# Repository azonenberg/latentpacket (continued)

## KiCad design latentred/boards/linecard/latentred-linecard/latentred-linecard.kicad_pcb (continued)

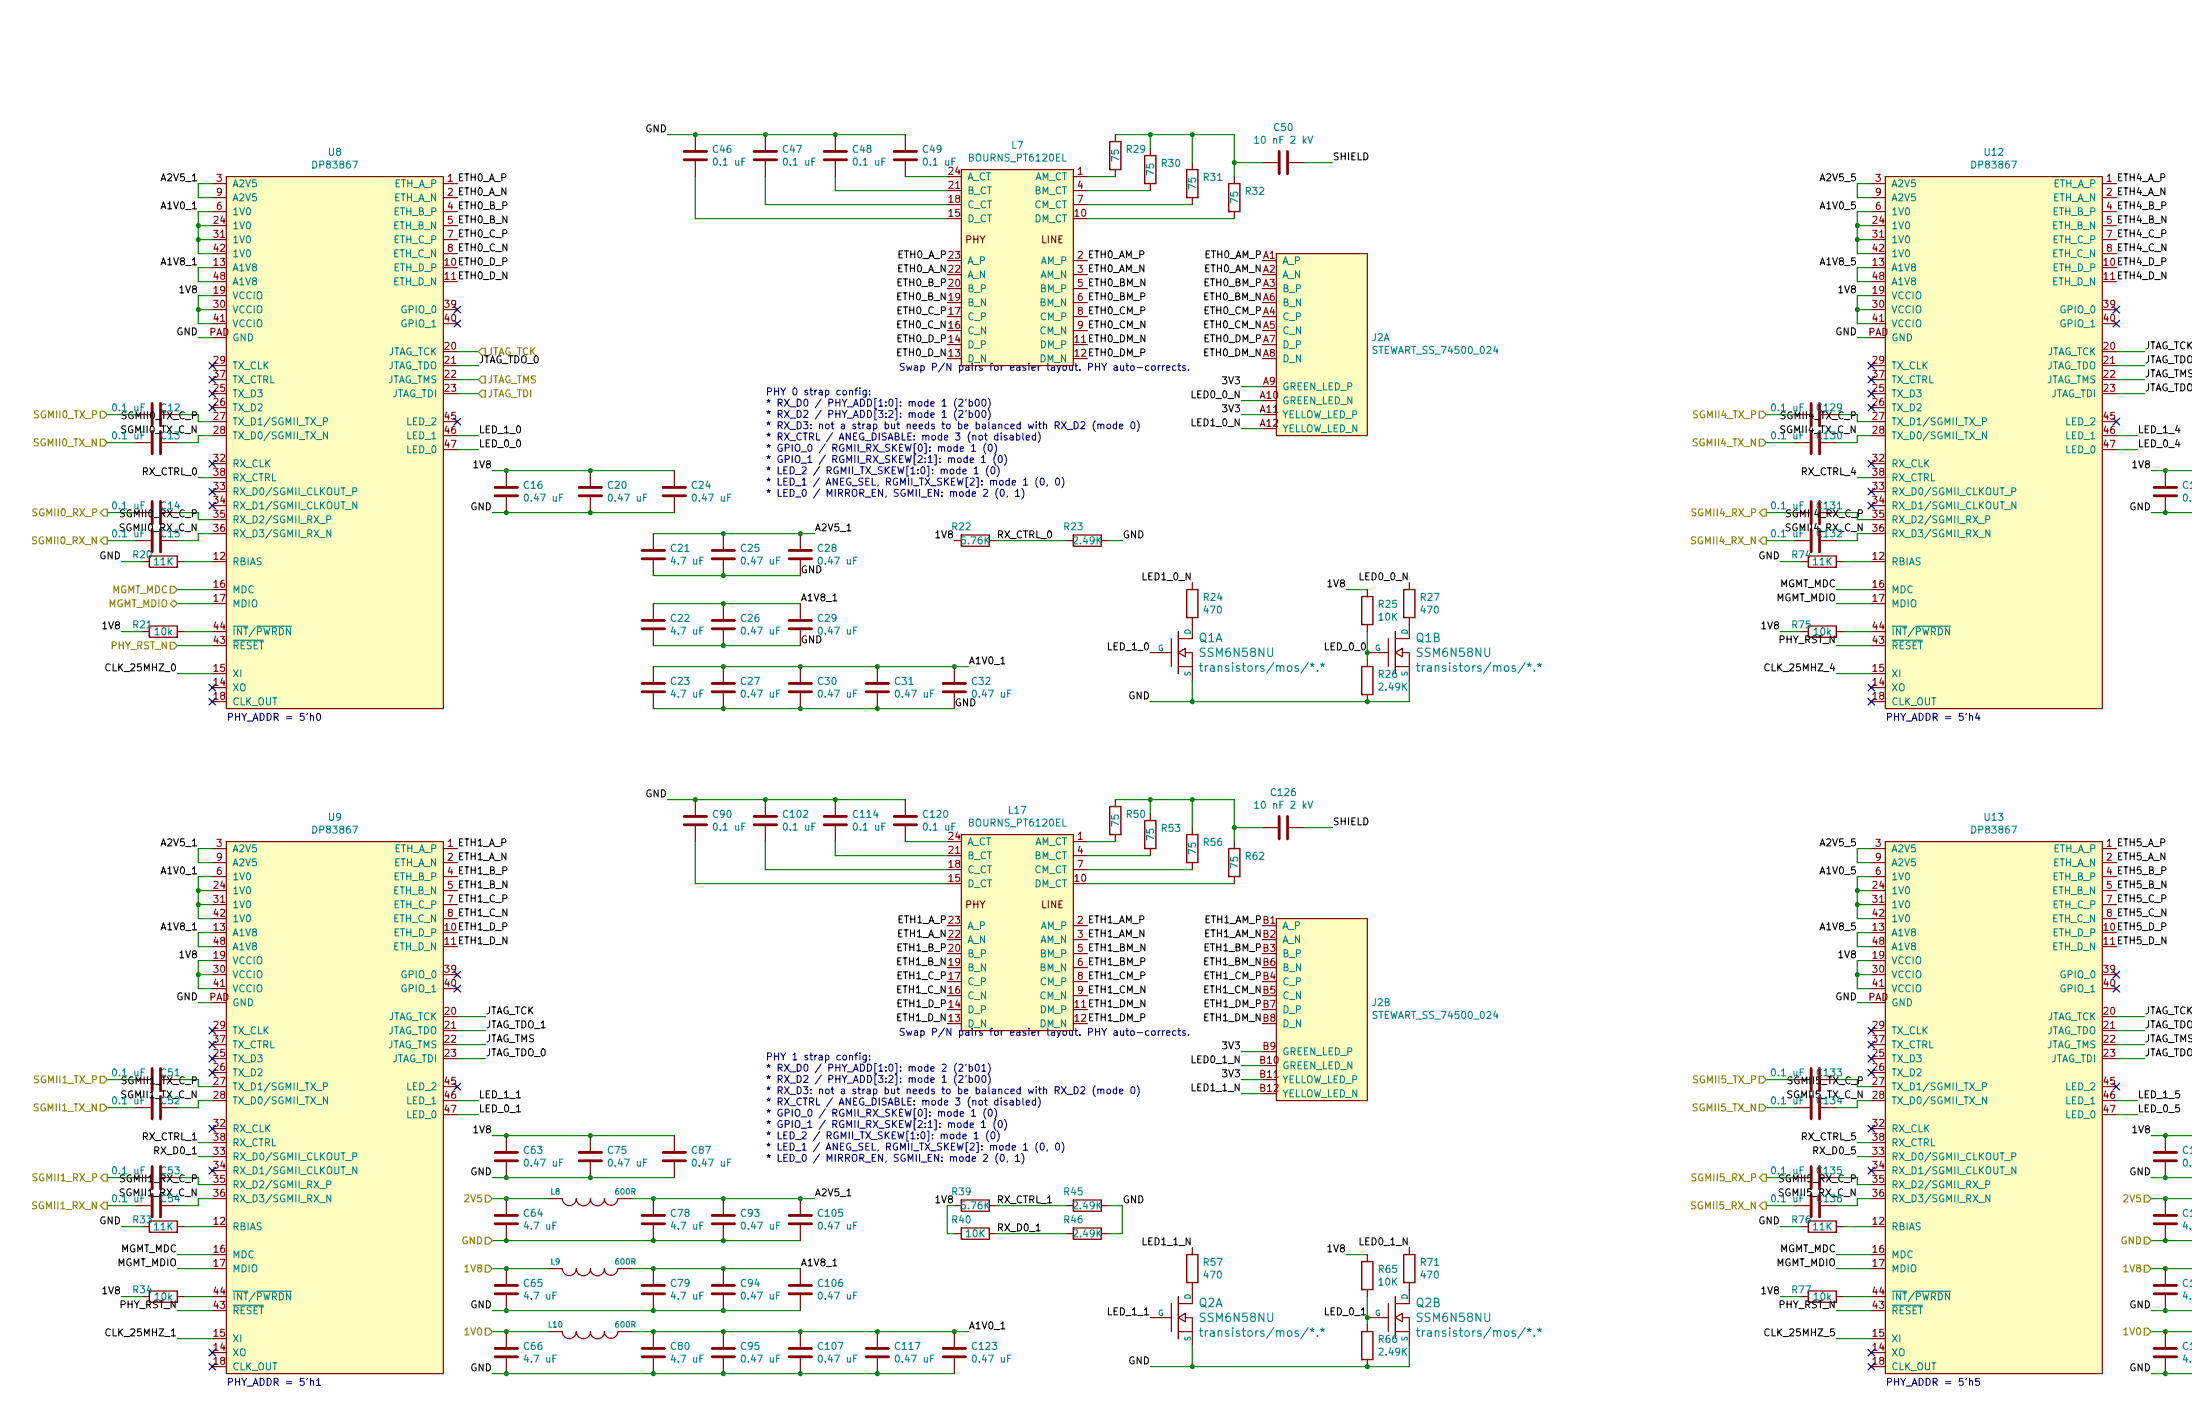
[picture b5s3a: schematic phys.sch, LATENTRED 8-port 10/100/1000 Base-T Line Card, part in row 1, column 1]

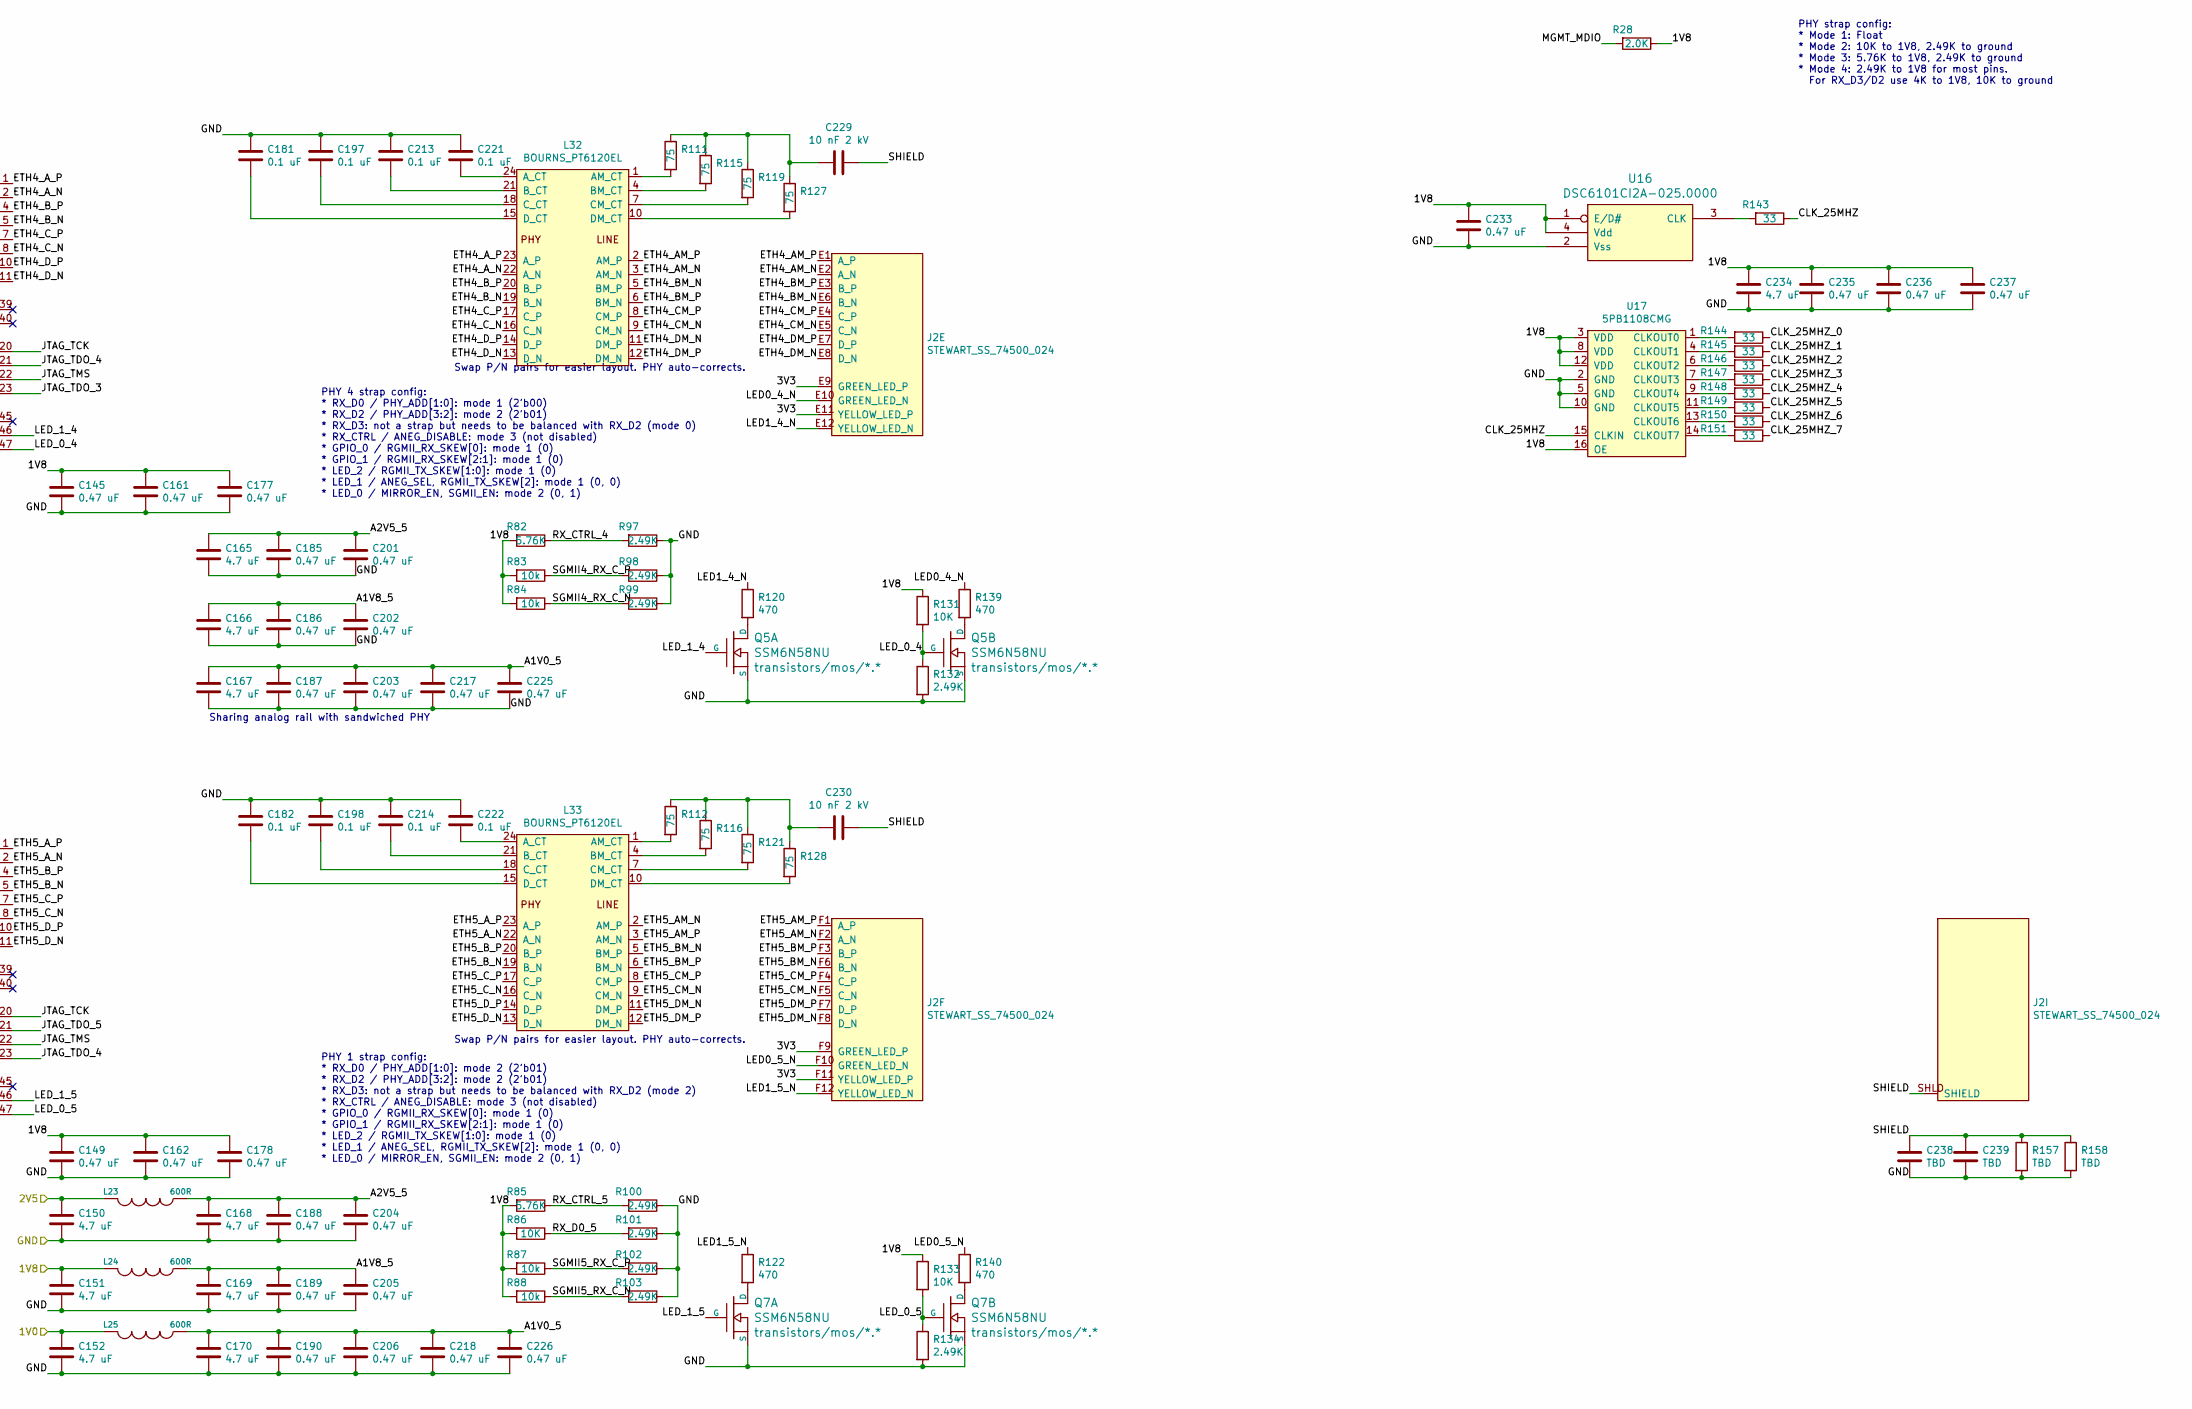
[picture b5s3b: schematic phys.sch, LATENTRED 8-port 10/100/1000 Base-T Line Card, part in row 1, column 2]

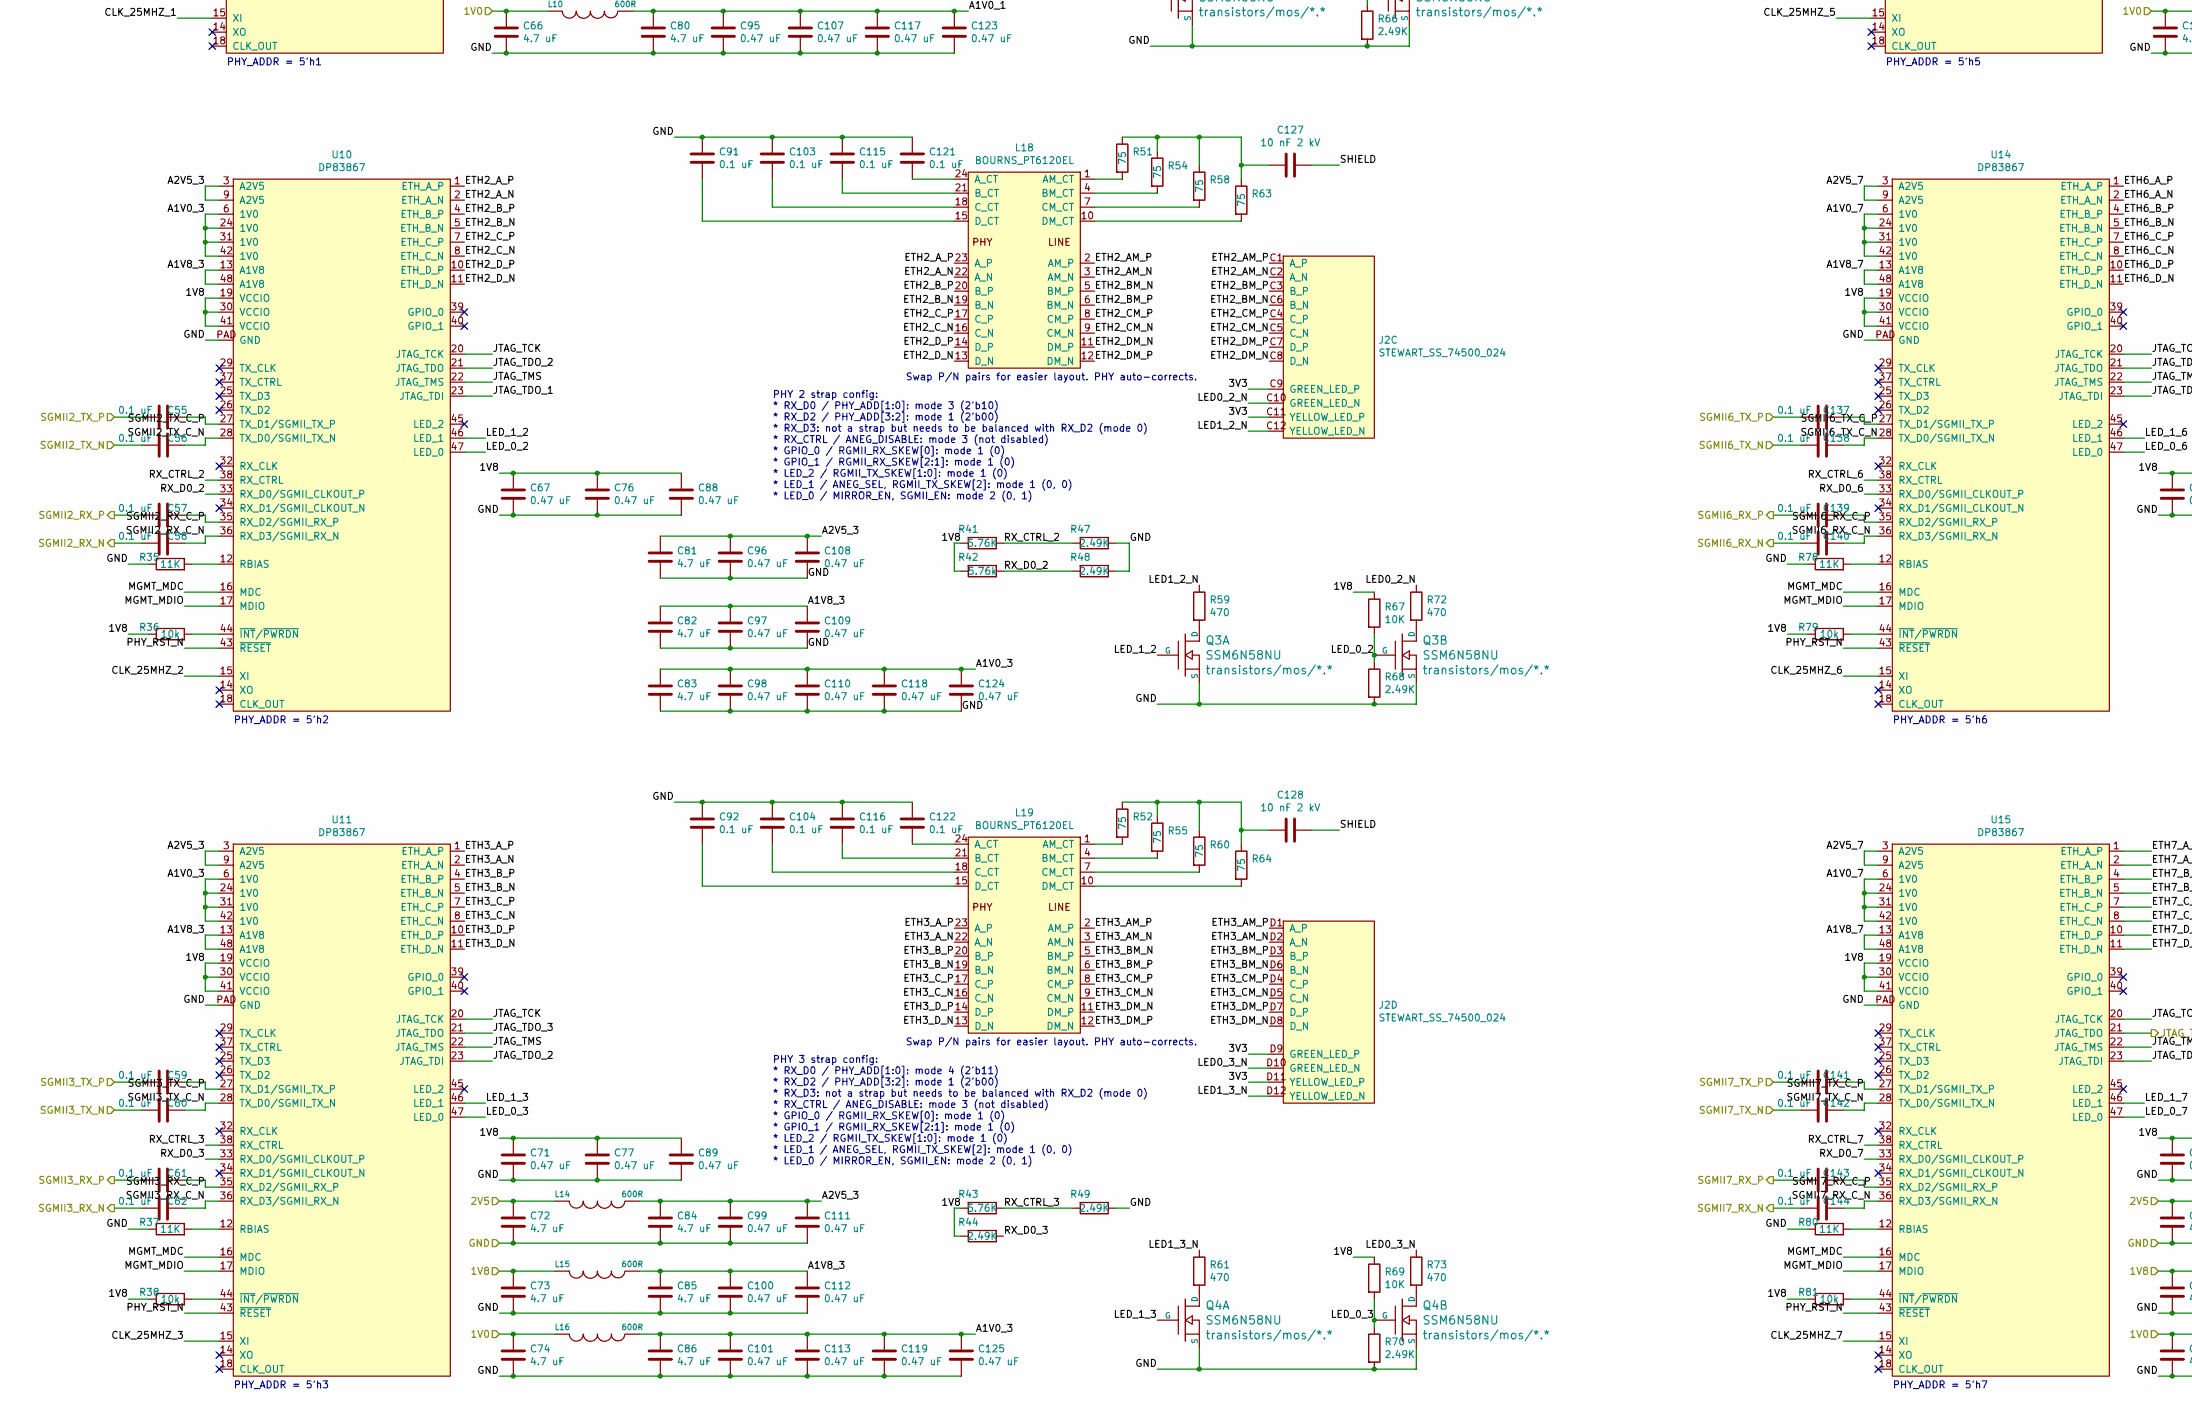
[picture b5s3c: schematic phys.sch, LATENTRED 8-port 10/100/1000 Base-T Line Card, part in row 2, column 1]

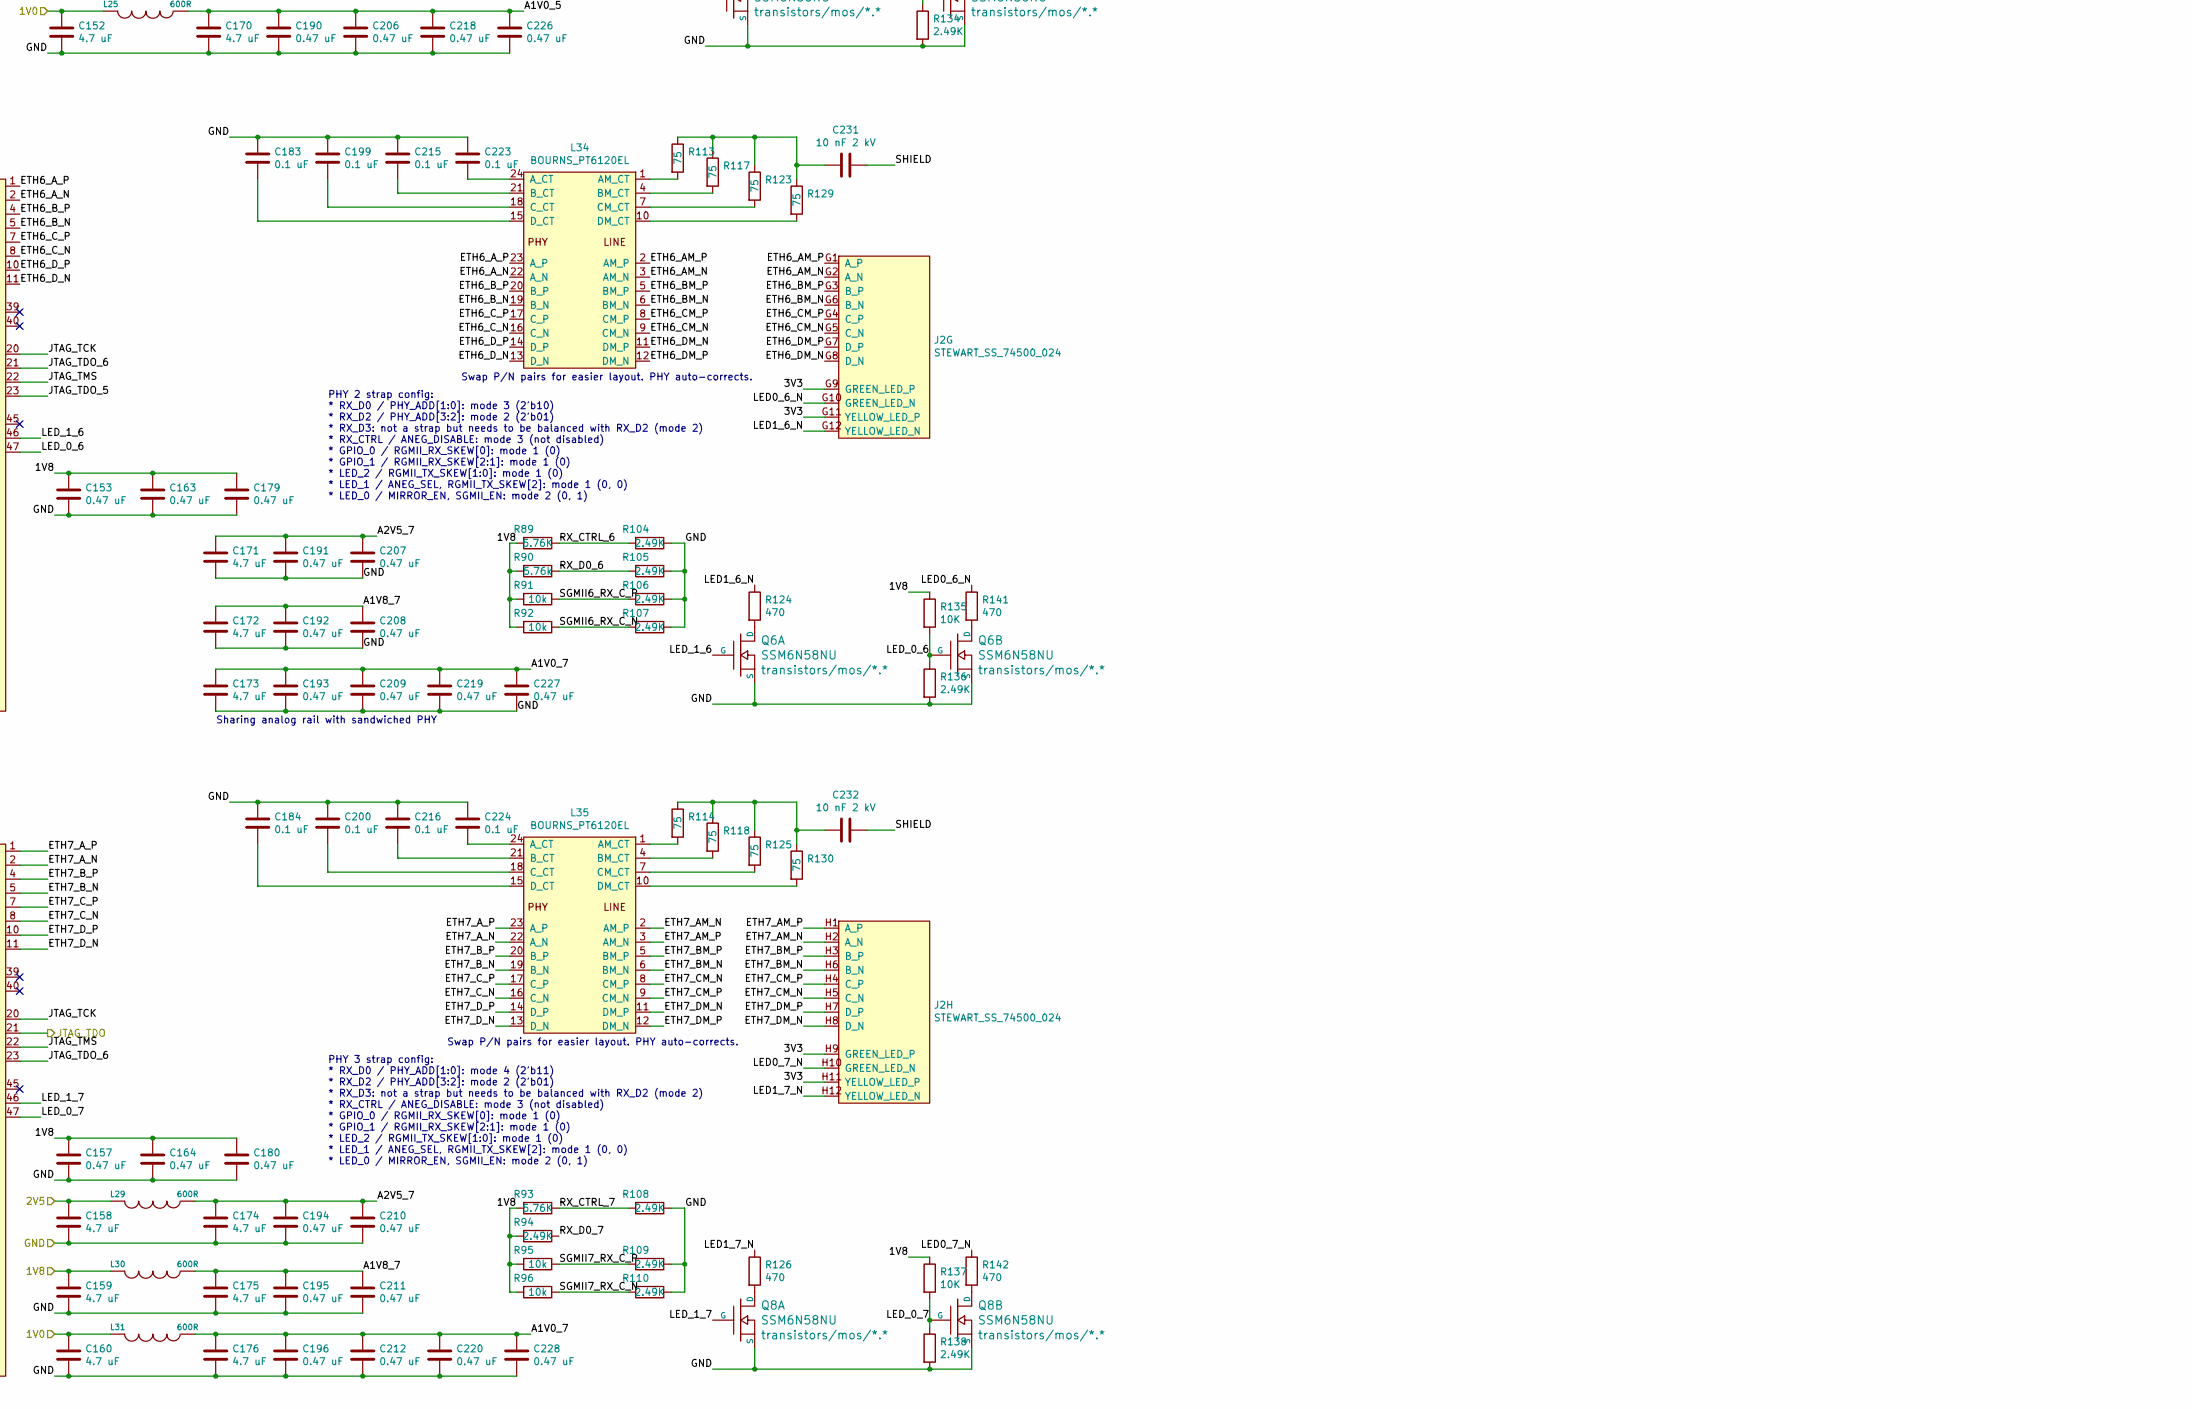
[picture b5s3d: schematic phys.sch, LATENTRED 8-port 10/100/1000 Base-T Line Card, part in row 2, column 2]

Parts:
C12, C13, C14, C15, C46, C47, C48, C49, C51, C52, C53, C54, C55, C56, C57, C58, C59, C60, C61, C62, C90, C91, C92, C102, C103, C104, C114, C115, C116, C120, C121, C122, C129, C130, C131, C132, C133, C134, C135, C136, C137, C138, C139, C140, C141, C142, C143, C144, C181, C182, C183, C184, C197, C198, C199, C200, C213, C214, C215, C216, C221, C222, C223, C224: 0.1 uF; EIA_0402_CAP_NOSILK
C16, C20, C24, C25, C26, C27, C28, C29, C30, C31, C32, C63, C67, C71, C75, C76, C77, C87, C88, C89, C93, C94, C95, C96, C97, C98, C99, C100, C101, C105, C106, C107, C108, C109, C110, C111, C112, C113, C117, C118, C119, C123, C124, C125, C145, C149, C153, C157, C161, C162, C163, C164, C177, C178, C179, C180, C185, C186, C187, C188, C189, C190, C191, C192, C193, C194, C195, C196, C201, C202, C203, C204, C205, C206, C207, C208, C209, C210, C211, C212, C217, C218, C219, C220, C225, C226, C227, C228, C233, C235, C236, C237: 0.47 uF; EIA_0402_CAP_NOSILK
C21, C22, C23, C64, C65, C66, C72, C73, C74, C78, C79, C80, C81, C82, C83, C84, C85, C86, C150, C151, C152, C158, C159, C160, C165, C166, C167, C168, C169, C170, C171, C172, C173, C174, C175, C176, C234: 4.7 uF; EIA_0603_CAP_NOSILK
C50, C126, C127, C128, C229, C230, C231, C232: 10 nF 2 kV; EIA_1812_CAP_NOSILK
C238, C239: TBD; EIA_1206_CAP_NOSILK
J2: STEWART_SS_74500_024; CONN_STEWART_SS_74500_024
L7, L17, L18, L19, L32, L33, L34, L35: BOURNS_PT6120EL; BOURNS_PT61020EL
L8, L9, L10, L14, L15, L16, L23, L24, L25, L29, L30, L31: 600R; EIA_0402_RES_NOSILK
Q1, Q2, Q3, Q4, Q5, Q6, Q7, Q8: SSM6N58NU; DFN_6_0.65MM_2x2MM_GDS
R20, R33, R35, R37, R74, R76, R78, R80: 11K; EIA_0402_RES_NOSILK
R21, R34, R36, R38, R75, R77, R79, R81, R83, R84, R87, R88, R91, R92, R95, R96: 10k; EIA_0402_RES_NOSILK
R22, R39, R41, R43, R82, R85, R89, R93: 5.76K; EIA_0402_RES_NOSILK
R23, R26, R44, R45, R46, R47, R48, R49, R66, R68, R70, R94, R97, R98, R99, R100, R101, R102, R103, R104, R105, R106, R107, R108, R109, R110, R132, R134, R136, R138: 2.49K; EIA_0402_RES_NOSILK
R24, R27, R57, R59, R61, R71, R72, R73, R120, R122, R124, R126, R139, R140, R141, R142: 470; EIA_0402_RES_NOSILK
R25, R40, R65, R67, R69, R86, R131, R133, R135, R137: 10K; EIA_0402_RES_NOSILK
R28: 2.0K; EIA_0402_RES_NOSILK
R29, R30, R31, R32, R50, R51, R52, R53, R54, R55, R56, R58, R60, R62, R63, R64, R111, R112, R113, R114, R115, R116, R117, R118, R119, R121, R123, R125, R127, R128, R129, R130: 75; EIA_0402_RES_NOSILK
R42, R90: 5.76k; EIA_0402_RES_NOSILK
R143, R144, R145, R146, R147, R148, R149, R150, R151: 33; EIA_0402_RES_NOSILK
R157, R158: TBD; EIA_1206_CAP_NOSILK
U8, U9, U10, U11, U12, U13, U14, U15: DP83867; QFN_48_0.5MM_7x7MM
U16: DSC6101CI2A-025.0000; OSCILLATOR_3.2x2.5
U17: 5PB1108CMG; QFN_16_0.4MM_2p5x2.5MM_NOPAD

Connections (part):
/GND: C16.2, C20.2, C21.2, C22.2, C23.2, C24.2, C25.2, C26.2, C27.2, C28.2, C29.2, C30.2, C31.2, C32.2, C46.1, C47.1, C48.1, C49.1, C63.2, C64.2, C65.2, C66.2, C67.2, C71.2, C72.2, C73.2, C74.2, C75.2, C76.2, C77.2, C78.2, C79.2, C80.2, C81.2, C82.2, C83.2, C84.2, C85.2, C86.2, C87.2, C88.2, C89.2, C90.1, C91.1, C92.1, C93.2, C94.2, C95.2, C96.2, C97.2, C98.2, C99.2, C100.2, C101.2, C102.1, C103.1, C104.1, C105.2, C106.2, C107.2, C108.2, C109.2, C110.2, C111.2, C112.2, C113.2, C114.1, C115.1, C116.1, C117.2, C118.2, C119.2, C120.1, C121.1, C122.1, C123.2, C124.2, C125.2, C145.2, C149.2, C150.2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; also elsewhere on the board
/JTAG_TCK: U8.20 (JTAG_TCK), U9.20 (JTAG_TCK), U10.20 (JTAG_TCK), U11.20 (JTAG_TCK), U12.20 (JTAG_TCK), U13.20 (JTAG_TCK), U14.20 (JTAG_TCK), U15.20 (JTAG_TCK); also elsewhere on the board
/JTAG_TDI: U8.23 (JTAG_TDI); also elsewhere on the board
/JTAG_TDO: U15.21 (JTAG_TDO); also elsewhere on the board
/JTAG_TMS: U8.22 (JTAG_TMS), U9.22 (JTAG_TMS), U10.22 (JTAG_TMS), U11.22 (JTAG_TMS), U12.22 (JTAG_TMS), U13.22 (JTAG_TMS), U14.22 (JTAG_TMS), U15.22 (JTAG_TMS); also elsewhere on the board
/MGMT_MDC: U8.16 (MDC), U9.16 (MDC), U10.16 (MDC), U11.16 (MDC), U12.16 (MDC), U13.16 (MDC), U14.16 (MDC), U15.16 (MDC); also elsewhere on the board
/MGMT_MDIO: R28.2, U8.17 (MDIO), U9.17 (MDIO), U10.17 (MDIO), U11.17 (MDIO), U12.17 (MDIO), U13.17 (MDIO), U14.17 (MDIO), U15.17 (MDIO); also elsewhere on the board
/PHY_RST_N: U8.43 (~RESET), U9.43 (~RESET), U10.43 (~RESET), U11.43 (~RESET), U12.43 (~RESET), U13.43 (~RESET), U14.43 (~RESET), U15.43 (~RESET); also elsewhere on the board
/PHYs/1V0: C66.1, C74.1, C152.1, C160.1, L10.2, L16.2, L25.2, L31.2; also elsewhere on the board
/PHYs/1V8: C16.1, C20.1, C24.1, C63.1, C65.1, C67.1, C71.1, C73.1, C75.1, C76.1, C77.1, C87.1, C88.1, C89.1, C145.1, C149.1, C151.1, C153.1, C157.1, C159.1, C161.1, C162.1, C163.1, C164.1, C177.1, C178.1, C179.1, C180.1, C233.1, C234.1, C235.1, C236.1, C237.1, L9.2, L15.2, L24.2, L30.2, R21.1, R22.2, R25.1, R28.1, R34.1, R36.1, R38.1, R39.2, R40.2, R41.2, R42.2, R43.2, R44.2, R65.1, R67.1, R69.1, R75.1, R77.1, R79.1, R81.1, R82.2, R83.2, R84.2, R85.2, R86.2, R87.2, R88.2, R89.2, R90.2, R91.2, R92.2, R93.2, R94.2, R95.2, R96.2, R131.1, R133.1, R135.1, R137.1, U8.19 (VCCIO), U8.30 (VCCIO), U8.41 (VCCIO), U9.19 (VCCIO), U9.30 (VCCIO)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; also elsewhere on the board
/PHYs/2V5: C64.1, C72.1, C150.1, C158.1, L8.2, L14.2, L23.2, L29.2; also elsewhere on the board
/PHYs/3V3: J2.A9 (GREEN_LED_P), J2.A11 (YELLOW_LED_P), J2.B9 (GREEN_LED_P), J2.B11 (YELLOW_LED_P), J2.C9 (GREEN_LED_P), J2.C11 (YELLOW_LED_P), J2.D9 (GREEN_LED_P), J2.D11 (YELLOW_LED_P), J2.E9 (GREEN_LED_P), J2.E11 (YELLOW_LED_P), J2.F9 (GREEN_LED_P), J2.F11 (YELLOW_LED_P), J2.G9 (GREEN_LED_P), J2.G11 (YELLOW_LED_P), J2.H9 (GREEN_LED_P), J2.H11 (YELLOW_LED_P)
/PHYs/A1V0_1: C23.1, C27.1, C30.1, C31.1, C32.1, C80.1, C95.1, C107.1, C117.1, C123.1, L10.1, U8.6 (1V0), U8.24 (1V0), U8.31 (1V0), U8.42 (1V0), U9.6 (1V0), U9.24 (1V0), U9.31 (1V0), U9.42 (1V0)
/PHYs/A1V0_3: C83.1, C86.1, C98.1, C101.1, C110.1, C113.1, C118.1, C119.1, C124.1, C125.1, L16.1, U10.6 (1V0), U10.24 (1V0), U10.31 (1V0), U10.42 (1V0), U11.6 (1V0), U11.24 (1V0), U11.31 (1V0), U11.42 (1V0)
/PHYs/A1V0_5: C167.1, C170.1, C187.1, C190.1, C203.1, C206.1, C217.1, C218.1, C225.1, C226.1, L25.1, U12.6 (1V0), U12.24 (1V0), U12.31 (1V0), U12.42 (1V0), U13.6 (1V0), U13.24 (1V0), U13.31 (1V0), U13.42 (1V0)
/PHYs/A1V0_7: C173.1, C176.1, C193.1, C196.1, C209.1, C212.1, C219.1, C220.1, C227.1, C228.1, L31.1, U14.6 (1V0), U14.24 (1V0), U14.31 (1V0), U14.42 (1V0), U15.6 (1V0), U15.24 (1V0), U15.31 (1V0), U15.42 (1V0)
/PHYs/A1V8_1: C22.1, C26.1, C29.1, C79.1, C94.1, C106.1, L9.1, U8.13 (A1V8), U8.48 (A1V8), U9.13 (A1V8), U9.48 (A1V8)
/PHYs/A1V8_3: C82.1, C85.1, C97.1, C100.1, C109.1, C112.1, L15.1, U10.13 (A1V8), U10.48 (A1V8), U11.13 (A1V8), U11.48 (A1V8)
/PHYs/A1V8_5: C166.1, C169.1, C186.1, C189.1, C202.1, C205.1, L24.1, U12.13 (A1V8), U12.48 (A1V8), U13.13 (A1V8), U13.48 (A1V8)
/PHYs/A1V8_7: C172.1, C175.1, C192.1, C195.1, C208.1, C211.1, L30.1, U14.13 (A1V8), U14.48 (A1V8), U15.13 (A1V8), U15.48 (A1V8)
/PHYs/A2V5_1: C21.1, C25.1, C28.1, C78.1, C93.1, C105.1, L8.1, U8.3 (A2V5), U8.9 (A2V5), U9.3 (A2V5), U9.9 (A2V5)
/PHYs/A2V5_3: C81.1, C84.1, C96.1, C99.1, C108.1, C111.1, L14.1, U10.3 (A2V5), U10.9 (A2V5), U11.3 (A2V5), U11.9 (A2V5)
/PHYs/A2V5_5: C165.1, C168.1, C185.1, C188.1, C201.1, C204.1, L23.1, U12.3 (A2V5), U12.9 (A2V5), U13.3 (A2V5), U13.9 (A2V5)
/PHYs/A2V5_7: C171.1, C174.1, C191.1, C194.1, C207.1, C210.1, L29.1, U14.3 (A2V5), U14.9 (A2V5), U15.3 (A2V5), U15.9 (A2V5)
/PHYs/CLK_25MHZ: R143.1, U17.15 (CLKIN)
/PHYs/CLK_25MHZ_0: R144.1, U8.15 (XI)
/PHYs/CLK_25MHZ_1: R145.1, U9.15 (XI)
/PHYs/CLK_25MHZ_2: R146.1, U10.15 (XI)
/PHYs/CLK_25MHZ_3: R147.1, U11.15 (XI)
/PHYs/CLK_25MHZ_4: R148.1, U12.15 (XI)
/PHYs/CLK_25MHZ_5: R149.1, U13.15 (XI)
/PHYs/CLK_25MHZ_6: R150.1, U14.15 (XI)
/PHYs/CLK_25MHZ_7: R151.1, U15.15 (XI)
/PHYs/ETH0_AM_N: J2.A2 (A_N), L7.3 (AM_N)
/PHYs/ETH0_AM_P: J2.A1 (A_P), L7.2 (AM_P)
/PHYs/ETH0_A_N: L7.22 (A_N), U8.2 (ETH_A_N)
/PHYs/ETH0_A_P: L7.23 (A_P), U8.1 (ETH_A_P)
/PHYs/ETH0_BM_N: J2.A6 (B_N), L7.5 (BM_P)
/PHYs/ETH0_BM_P: J2.A3 (B_P), L7.6 (BM_N)
/PHYs/ETH0_B_N: L7.19 (B_N), U8.5 (ETH_B_N)
/PHYs/ETH0_B_P: L7.20 (B_P), U8.4 (ETH_B_P)
/PHYs/ETH0_CM_N: J2.A5 (C_N), L7.9 (CM_N)
/PHYs/ETH0_CM_P: J2.A4 (C_P), L7.8 (CM_P)
/PHYs/ETH0_C_N: L7.16 (C_N), U8.8 (ETH_C_N)
/PHYs/ETH0_C_P: L7.17 (C_P), U8.7 (ETH_C_P)
/PHYs/ETH0_DM_N: J2.A8 (D_N), L7.11 (DM_P)
/PHYs/ETH0_DM_P: J2.A7 (D_P), L7.12 (DM_N)
/PHYs/ETH0_D_N: L7.13 (D_N), U8.11 (ETH_D_N)
/PHYs/ETH0_D_P: L7.14 (D_P), U8.10 (ETH_D_P)
/PHYs/ETH1_AM_N: J2.B2 (A_N), L17.3 (AM_N)
/PHYs/ETH1_AM_P: J2.B1 (A_P), L17.2 (AM_P)
/PHYs/ETH1_A_N: L17.22 (A_N), U9.2 (ETH_A_N)
/PHYs/ETH1_A_P: L17.23 (A_P), U9.1 (ETH_A_P)
/PHYs/ETH1_BM_N: J2.B6 (B_N), L17.5 (BM_P)
/PHYs/ETH1_BM_P: J2.B3 (B_P), L17.6 (BM_N)
/PHYs/ETH1_B_N: L17.19 (B_N), U9.5 (ETH_B_N)
/PHYs/ETH1_B_P: L17.20 (B_P), U9.4 (ETH_B_P)
/PHYs/ETH1_CM_N: J2.B5 (C_N), L17.9 (CM_N)
/PHYs/ETH1_CM_P: J2.B4 (C_P), L17.8 (CM_P)
/PHYs/ETH1_C_N: L17.16 (C_N), U9.8 (ETH_C_N)
/PHYs/ETH1_C_P: L17.17 (C_P), U9.7 (ETH_C_P)
/PHYs/ETH1_DM_N: J2.B8 (D_N), L17.11 (DM_P)
/PHYs/ETH1_DM_P: J2.B7 (D_P), L17.12 (DM_N)
/PHYs/ETH1_D_N: L17.13 (D_N), U9.11 (ETH_D_N)
/PHYs/ETH1_D_P: L17.14 (D_P), U9.10 (ETH_D_P)
/PHYs/ETH2_AM_N: J2.C2 (A_N), L18.3 (AM_N)
/PHYs/ETH2_AM_P: J2.C1 (A_P), L18.2 (AM_P)
/PHYs/ETH2_A_N: L18.22 (A_N), U10.2 (ETH_A_N)
/PHYs/ETH2_A_P: L18.23 (A_P), U10.1 (ETH_A_P)
/PHYs/ETH2_BM_N: J2.C6 (B_N), L18.5 (BM_P)
/PHYs/ETH2_BM_P: J2.C3 (B_P), L18.6 (BM_N)
/PHYs/ETH2_B_N: L18.19 (B_N), U10.5 (ETH_B_N)
/PHYs/ETH2_B_P: L18.20 (B_P), U10.4 (ETH_B_P)
/PHYs/ETH2_CM_N: J2.C5 (C_N), L18.9 (CM_N)
/PHYs/ETH2_CM_P: J2.C4 (C_P), L18.8 (CM_P)
/PHYs/ETH2_C_N: L18.16 (C_N), U10.8 (ETH_C_N)
/PHYs/ETH2_C_P: L18.17 (C_P), U10.7 (ETH_C_P)
/PHYs/ETH2_DM_N: J2.C8 (D_N), L18.11 (DM_P)
/PHYs/ETH2_DM_P: J2.C7 (D_P), L18.12 (DM_N)
/PHYs/ETH2_D_N: L18.13 (D_N), U10.11 (ETH_D_N)
/PHYs/ETH2_D_P: L18.14 (D_P), U10.10 (ETH_D_P)
/PHYs/ETH3_AM_N: J2.D2 (A_N), L19.3 (AM_N)
/PHYs/ETH3_AM_P: J2.D1 (A_P), L19.2 (AM_P)
/PHYs/ETH3_A_N: L19.22 (A_N), U11.2 (ETH_A_N)
/PHYs/ETH3_A_P: L19.23 (A_P), U11.1 (ETH_A_P)
/PHYs/ETH3_BM_N: J2.D6 (B_N), L19.5 (BM_P)
/PHYs/ETH3_BM_P: J2.D3 (B_P), L19.6 (BM_N)
/PHYs/ETH3_B_N: L19.19 (B_N), U11.5 (ETH_B_N)
/PHYs/ETH3_B_P: L19.20 (B_P), U11.4 (ETH_B_P)
/PHYs/ETH3_CM_N: J2.D5 (C_N), L19.9 (CM_N)
/PHYs/ETH3_CM_P: J2.D4 (C_P), L19.8 (CM_P)
/PHYs/ETH3_C_N: L19.16 (C_N), U11.8 (ETH_C_N)
/PHYs/ETH3_C_P: L19.17 (C_P), U11.7 (ETH_C_P)
/PHYs/ETH3_DM_N: J2.D8 (D_N), L19.11 (DM_P)
/PHYs/ETH3_DM_P: J2.D7 (D_P), L19.12 (DM_N)
/PHYs/ETH3_D_N: L19.13 (D_N), U11.11 (ETH_D_N)
/PHYs/ETH3_D_P: L19.14 (D_P), U11.10 (ETH_D_P)
/PHYs/ETH4_AM_N: J2.E2 (A_N), L32.3 (AM_N)
/PHYs/ETH4_AM_P: J2.E1 (A_P), L32.2 (AM_P)
/PHYs/ETH4_A_N: L32.22 (A_N), U12.2 (ETH_A_N)
/PHYs/ETH4_A_P: L32.23 (A_P), U12.1 (ETH_A_P)
/PHYs/ETH4_BM_N: J2.E6 (B_N), L32.5 (BM_P)
/PHYs/ETH4_BM_P: J2.E3 (B_P), L32.6 (BM_N)
/PHYs/ETH4_B_N: L32.19 (B_N), U12.5 (ETH_B_N)
/PHYs/ETH4_B_P: L32.20 (B_P), U12.4 (ETH_B_P)
/PHYs/ETH4_CM_N: J2.E5 (C_N), L32.9 (CM_N)
/PHYs/ETH4_CM_P: J2.E4 (C_P), L32.8 (CM_P)
/PHYs/ETH4_C_N: L32.16 (C_N), U12.8 (ETH_C_N)
/PHYs/ETH4_C_P: L32.17 (C_P), U12.7 (ETH_C_P)
/PHYs/ETH4_DM_N: J2.E8 (D_N), L32.11 (DM_P)
/PHYs/ETH4_DM_P: J2.E7 (D_P), L32.12 (DM_N)
/PHYs/ETH4_D_N: L32.13 (D_N), U12.11 (ETH_D_N)
/PHYs/ETH4_D_P: L32.14 (D_P), U12.10 (ETH_D_P)
/PHYs/ETH5_AM_N: J2.F2 (A_N), L33.2 (AM_P)
/PHYs/ETH5_AM_P: J2.F1 (A_P), L33.3 (AM_N)
/PHYs/ETH5_A_N: L33.22 (A_N), U13.2 (ETH_A_N)
/PHYs/ETH5_A_P: L33.23 (A_P), U13.1 (ETH_A_P)
/PHYs/ETH5_BM_N: J2.F6 (B_N), L33.5 (BM_P)
/PHYs/ETH5_BM_P: J2.F3 (B_P), L33.6 (BM_N)
/PHYs/ETH5_B_N: L33.19 (B_N), U13.5 (ETH_B_N)
/PHYs/ETH5_B_P: L33.20 (B_P), U13.4 (ETH_B_P)
/PHYs/ETH5_CM_N: J2.F5 (C_N), L33.9 (CM_N)
/PHYs/ETH5_CM_P: J2.F4 (C_P), L33.8 (CM_P)
/PHYs/ETH5_C_N: L33.16 (C_N), U13.8 (ETH_C_N)
/PHYs/ETH5_C_P: L33.17 (C_P), U13.7 (ETH_C_P)
/PHYs/ETH5_DM_N: J2.F8 (D_N), L33.11 (DM_P)
/PHYs/ETH5_DM_P: J2.F7 (D_P), L33.12 (DM_N)
/PHYs/ETH5_D_N: L33.13 (D_N), U13.11 (ETH_D_N)
/PHYs/ETH5_D_P: L33.14 (D_P), U13.10 (ETH_D_P)
/PHYs/ETH6_AM_N: J2.G2 (A_N), L34.3 (AM_N)
/PHYs/ETH6_AM_P: J2.G1 (A_P), L34.2 (AM_P)
/PHYs/ETH6_A_N: L34.22 (A_N), U14.2 (ETH_A_N)
/PHYs/ETH6_A_P: L34.23 (A_P), U14.1 (ETH_A_P)
/PHYs/ETH6_BM_N: J2.G6 (B_N), L34.6 (BM_N)
/PHYs/ETH6_BM_P: J2.G3 (B_P), L34.5 (BM_P)
/PHYs/ETH6_B_N: L34.19 (B_N), U14.5 (ETH_B_N)
/PHYs/ETH6_B_P: L34.20 (B_P), U14.4 (ETH_B_P)
/PHYs/ETH6_CM_N: J2.G5 (C_N), L34.9 (CM_N)
/PHYs/ETH6_CM_P: J2.G4 (C_P), L34.8 (CM_P)
/PHYs/ETH6_C_N: L34.16 (C_N), U14.8 (ETH_C_N)
/PHYs/ETH6_C_P: L34.17 (C_P), U14.7 (ETH_C_P)
/PHYs/ETH6_DM_N: J2.G8 (D_N), L34.11 (DM_P)
/PHYs/ETH6_DM_P: J2.G7 (D_P), L34.12 (DM_N)
/PHYs/ETH6_D_N: L34.13 (D_N), U14.11 (ETH_D_N)
/PHYs/ETH6_D_P: L34.14 (D_P), U14.10 (ETH_D_P)
/PHYs/ETH7_AM_N: J2.H2 (A_N), L35.2 (AM_P)
/PHYs/ETH7_AM_P: J2.H1 (A_P), L35.3 (AM_N)
/PHYs/ETH7_A_N: L35.22 (A_N), U15.2 (ETH_A_N)
/PHYs/ETH7_A_P: L35.23 (A_P), U15.1 (ETH_A_P)
/PHYs/ETH7_BM_N: J2.H6 (B_N), L35.6 (BM_N)
/PHYs/ETH7_BM_P: J2.H3 (B_P), L35.5 (BM_P)
/PHYs/ETH7_B_N: L35.19 (B_N), U15.5 (ETH_B_N)
/PHYs/ETH7_B_P: L35.20 (B_P), U15.4 (ETH_B_P)
/PHYs/ETH7_CM_N: J2.H5 (C_N), L35.8 (CM_P)
/PHYs/ETH7_CM_P: J2.H4 (C_P), L35.9 (CM_N)
/PHYs/ETH7_C_N: L35.16 (C_N), U15.8 (ETH_C_N)
/PHYs/ETH7_C_P: L35.17 (C_P), U15.7 (ETH_C_P)
/PHYs/ETH7_DM_N: J2.H8 (D_N), L35.11 (DM_P)
/PHYs/ETH7_DM_P: J2.H7 (D_P), L35.12 (DM_N)
/PHYs/ETH7_D_N: L35.13 (D_N), U15.11 (ETH_D_N)
/PHYs/ETH7_D_P: L35.14 (D_P), U15.10 (ETH_D_P)
/PHYs/JTAG_TDO_0: U8.21 (JTAG_TDO), U9.23 (JTAG_TDI)
/PHYs/JTAG_TDO_1: U9.21 (JTAG_TDO), U10.23 (JTAG_TDI)
/PHYs/JTAG_TDO_2: U10.21 (JTAG_TDO), U11.23 (JTAG_TDI)
/PHYs/JTAG_TDO_3: U11.21 (JTAG_TDO), U12.23 (JTAG_TDI)
/PHYs/JTAG_TDO_4: U12.21 (JTAG_TDO), U13.23 (JTAG_TDI)
/PHYs/JTAG_TDO_5: U13.21 (JTAG_TDO), U14.23 (JTAG_TDI)
/PHYs/JTAG_TDO_6: U14.21 (JTAG_TDO), U15.23 (JTAG_TDI)
/PHYs/LED0_0_N: J2.A10 (GREEN_LED_N), R27.1
/PHYs/LED0_1_N: J2.B10 (GREEN_LED_N), R71.1
/PHYs/LED0_2_N: J2.C10 (GREEN_LED_N), R72.1
/PHYs/LED0_3_N: J2.D10 (GREEN_LED_N), R73.1
/PHYs/LED0_4_N: J2.E10 (GREEN_LED_N), R139.1
/PHYs/LED0_5_N: J2.F10 (GREEN_LED_N), R140.1
/PHYs/LED0_6_N: J2.G10 (GREEN_LED_N), R141.1
/PHYs/LED0_7_N: J2.H10 (GREEN_LED_N), R142.1
/PHYs/LED1_0_N: J2.A12 (YELLOW_LED_N), R24.1
/PHYs/LED1_1_N: J2.B12 (YELLOW_LED_N), R57.1
/PHYs/LED1_2_N: J2.C12 (YELLOW_LED_N), R59.1
/PHYs/LED1_3_N: J2.D12 (YELLOW_LED_N), R61.1
/PHYs/LED1_4_N: J2.E12 (YELLOW_LED_N), R120.1
/PHYs/LED1_5_N: J2.F12 (YELLOW_LED_N), R122.1
/PHYs/LED1_6_N: J2.G12 (YELLOW_LED_N), R124.1
/PHYs/LED1_7_N: J2.H12 (YELLOW_LED_N), R126.1
/PHYs/LED_0_0: Q1.G2 (G), R25.2, R26.1, U8.47 (LED_0)
/PHYs/LED_0_1: Q2.G2 (G), R65.2, R66.1, U9.47 (LED_0)
/PHYs/LED_0_2: Q3.G2 (G), R67.2, R68.1, U10.47 (LED_0)
/PHYs/LED_0_3: Q4.G2 (G), R69.2, R70.1, U11.47 (LED_0)
/PHYs/LED_0_4: Q5.G2 (G), R131.2, R132.1, U12.47 (LED_0)
/PHYs/LED_0_5: Q7.G2 (G), R133.2, R134.1, U13.47 (LED_0)
/PHYs/LED_0_6: Q6.G2 (G), R135.2, R136.1, U14.47 (LED_0)
/PHYs/LED_0_7: Q8.G2 (G), R137.2, R138.1, U15.47 (LED_0)
/PHYs/LED_1_0: Q1.G1 (G), U8.46 (LED_1)
/PHYs/LED_1_1: Q2.G1 (G), U9.46 (LED_1)
/PHYs/LED_1_2: Q3.G1 (G), U10.46 (LED_1)
/PHYs/LED_1_3: Q4.G1 (G), U11.46 (LED_1)
/PHYs/LED_1_4: Q5.G1 (G), U12.46 (LED_1)
/PHYs/LED_1_5: Q7.G1 (G), U13.46 (LED_1)
/PHYs/LED_1_6: Q6.G1 (G), U14.46 (LED_1)
/PHYs/LED_1_7: Q8.G1 (G), U15.46 (LED_1)
/PHYs/RX_CTRL_0: R22.1, R23.2, U8.38 (RX_CTRL)
/PHYs/RX_CTRL_1: R39.1, R45.2, U9.38 (RX_CTRL)
/PHYs/RX_CTRL_2: R41.1, R47.2, U10.38 (RX_CTRL)
/PHYs/RX_CTRL_3: R43.1, R49.2, U11.38 (RX_CTRL)
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
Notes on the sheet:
PHY 0 strap config: * RX_D0 / PHY_ADD[1:0]: mode 1 (2'b00) * RX_D2 / PHY_ADD[3:2]: mode 1 (2'b00) * RX_D3: not a strap but needs to be balanced with RX_D2 (mode 0) * RX_CTRL / ANEG_DISABLE: mode 3 (not disabled) * GPIO_0 / RGMII_RX_SKEW[0]: mode 1 (0) * GPIO_1 / RGMII_RX_SKEW[2:1]: mode 1 (0) * LED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
PHY strap config: * Mode 1: Float * Mode 2: 10K to 1V8, 2.49K to ground * Mode 3: 5.76K to 1V8, 2.49K to ground * Mode 4: 2.49K to 1V8 for most pins. For RX_D3/D2 use 4K to 1V8, 10K to ground
PHY 1 strap config: * RX_D0 / PHY_ADD[1:0]: mode 2 (2'b01) * RX_D2 / PHY_ADD[3:2]: mode 1 (2'b00) * RX_D3: not a strap but needs to be balanced with RX_D2 (mode 0) * RX_CTRL / ANEG_DISABLE: mode 3 (not disabled) * GPIO_0 / RGMII_RX_SKEW[0]: mode 1 (0) * GPIO_1 / RGMII_RX_SKEW[2:1]: mode 1 (0) * LED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
PHY_ADDR = 5'h0
PHY_ADDR = 5'h1
PHY 2 strap config: * RX_D0 / PHY_ADD[1:0]: mode 3 (2'b10) * RX_D2 / PHY_ADD[3:2]: mode 1 (2'b00) * RX_D3: not a strap but needs to be balanced with RX_D2 (mode 0) * RX_CTRL / ANEG_DISABLE: mode 3 (not disabled) * GPIO_0 / RGMII_RX_SKEW[0]: mode 1 (0) * GPIO_1 / RGMII_RX_SKEW[2:1]: mode 1 (0) * LED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
PHY_ADDR = 5'h2
PHY 3 strap config: * RX_D0 / PHY_ADD[1:0]: mode 4 (2'b11) * RX_D2 / PHY_ADD[3:2]: mode 1 (2'b00) * RX_D3: not a strap but needs to be balanced with RX_D2 (mode 0) * RX_CTRL / ANEG_DISABLE: mode 3 (not disabled) * GPIO_0 / RGMII_RX_SKEW[0]: mode 1 (0) * GPIO_1 / RGMII_RX_SKEW[2:1]: mode 1 (0) * LED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
PHY_ADDR = 5'h3
PHY 4 strap config: * RX_D0 / PHY_ADD[1:0]: mode 1 (2'b00) * RX_D2 / PHY_ADD[3:2]: mode 2 (2'b01) * RX_D3: not a strap but needs to be balanced with RX_D2 (mode 0) * RX_CTRL / ANEG_DISABLE: mode 3 (not disabled) * GPIO_0 / RGMII_RX_SKEW[0]: mode 1 (0) * GPIO_1 / RGMII_RX_SKEW[2:1]: mode 1 (0) * LED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
PHY 1 strap config: * RX_D0 / PHY_ADD[1:0]: mode 2 (2'b01) * RX_D2 / PHY_ADD[3:2]: mode 2 (2'b01) * RX_D3: not a strap but needs to be balanced with RX_D2 (mode 2) * RX_CTRL / ANEG_DISABLE: mode 3 (not disabled) * GPIO_0 / RGMII_RX_SKEW[0]: mode 1 (0) * GPIO_1 / RGMII_RX_SKEW[2:1]: mode 1 (0) * LED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
PHY_ADDR = 5'h4
PHY_ADDR = 5'h5
PHY 2 strap config: * RX_D0 / PHY_ADD[1:0]: mode 3 (2'b10) * RX_D2 / PHY_ADD[3:2]: mode 2 (2'b01) * RX_D3: not a strap but needs to be balanced with RX_D2 (mode 2) * RX_CTRL / ANEG_DISABLE: mode 3 (not disabled) * GPIO_0 / RGMII_RX_SKEW[0]: mode 1 (0) * GPIO_1 / RGMII_RX_SKEW[2:1]: mode 1 (0) * LED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
PHY_ADDR = 5'h6
PHY 3 strap config: * RX_D0 / PHY_ADD[1:0]: mode 4 (2'b11) * RX_D2 / PHY_ADD[3:2]: mode 2 (2'b01) * RX_D3: not a strap but needs to be balanced with RX_D2 (mode 2) * RX_CTRL / ANEG_DISABLE: mode 3 (not disabled) * GPIO_0 / RGMII_RX_SKEW[0]: mode 1 (0) * GPIO_1 / RGMII_RX_SKEW[2:1]: mode 1 (0) * LED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
PHY_ADDR = 5'h7
Swap P/N pairs for easier layout. PHY auto-corrects.
Sharing analog rail with sandwiched PHY
